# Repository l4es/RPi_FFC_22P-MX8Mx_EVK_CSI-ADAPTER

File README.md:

# RPi_FFC_22P-MX8Mx_EVK_CSI-ADAPTER

Adapter for Raspberry Pi compatible camera modules to iMX MiniSAS 36-pin camera interface, available in official NXP EVKs.

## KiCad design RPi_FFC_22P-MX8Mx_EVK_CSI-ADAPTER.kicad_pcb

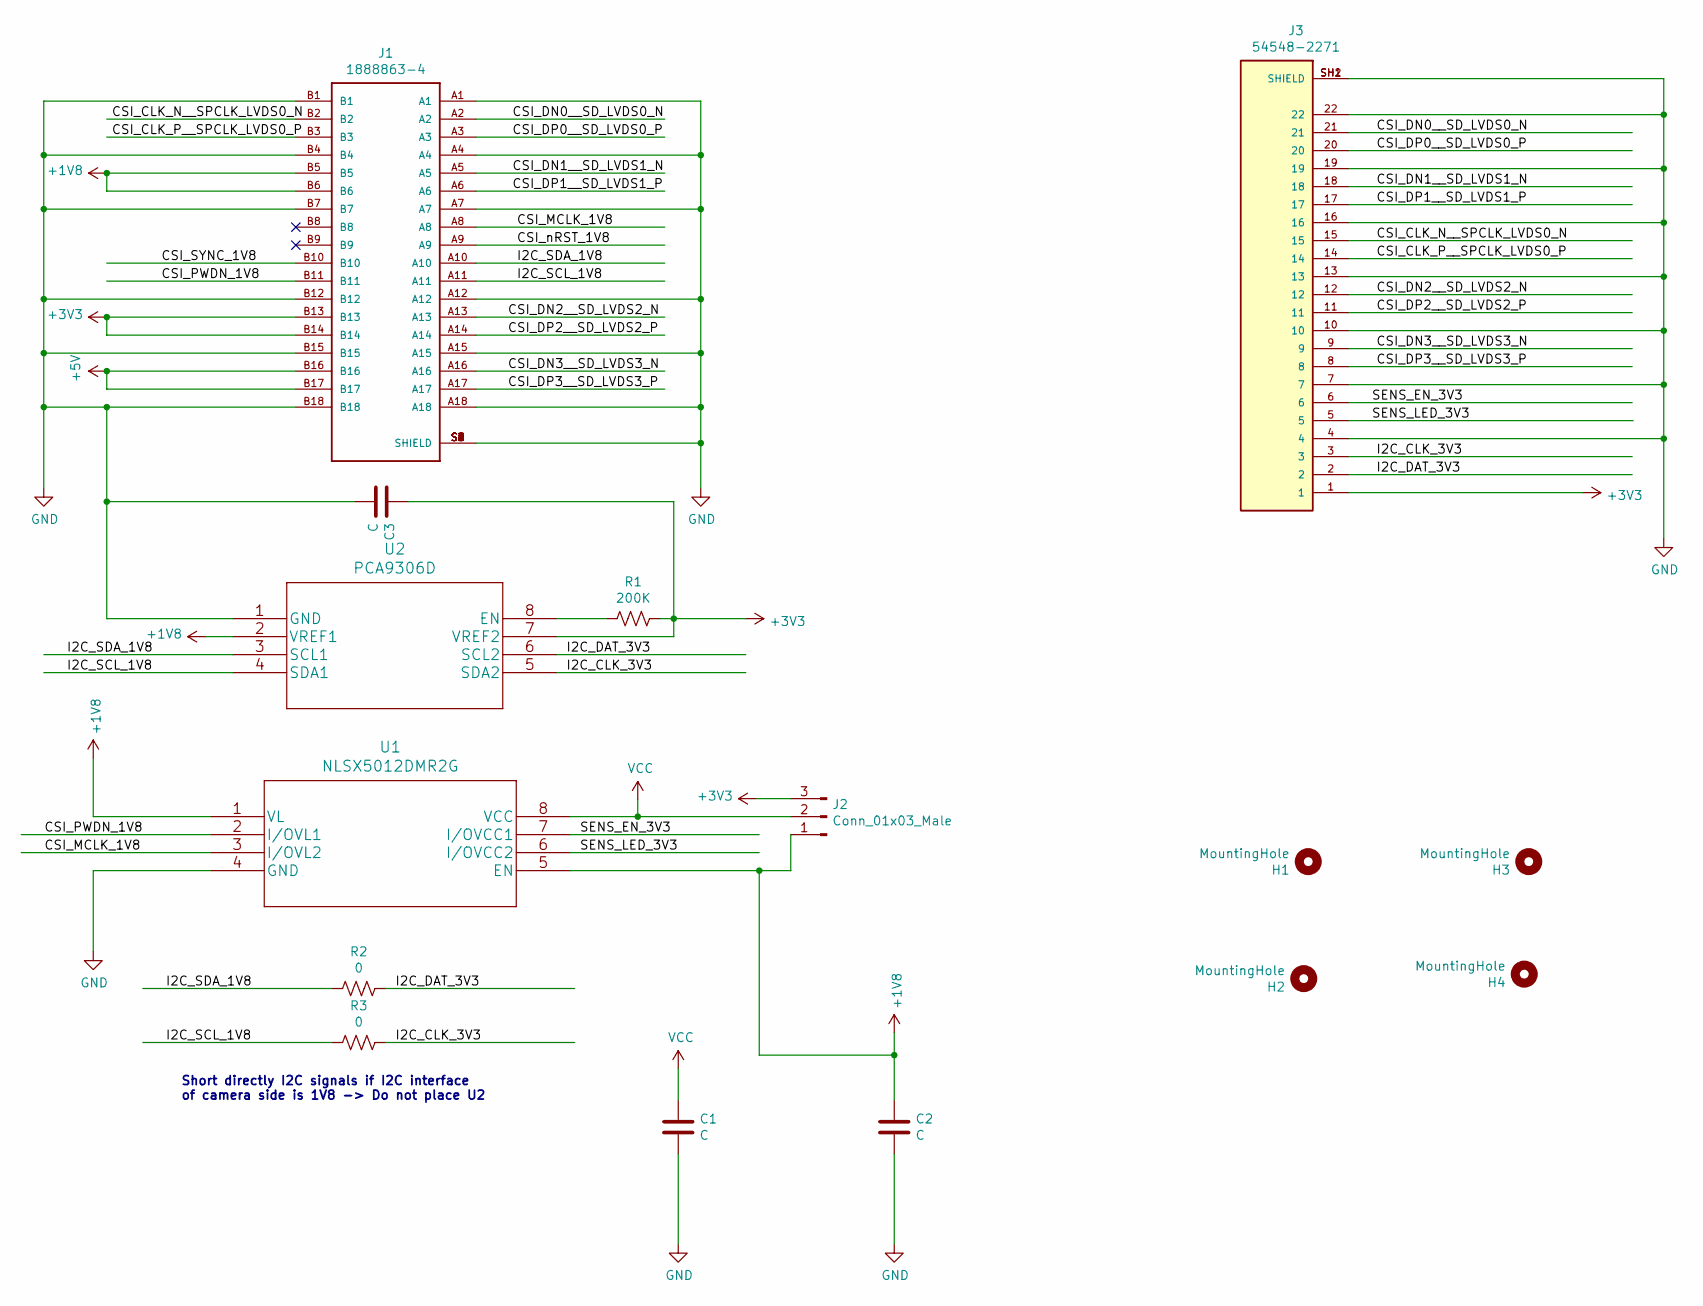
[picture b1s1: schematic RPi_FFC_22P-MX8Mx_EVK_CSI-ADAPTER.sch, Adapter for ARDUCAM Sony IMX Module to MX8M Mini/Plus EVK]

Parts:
C1, C2, C3: C; C_0603_1608Metric_Pad1.08x0.95mm_HandSolder
H1, H2, H3, H4: MountingHole; MountingHole_2.2mm_M2_Pad
J1: 1888863-4; TE_1888863-4
J2: Conn_01x03_Male; PinHeader_1x03_P2.54mm_Vertical
J3: 54548-2271; MOLEX_54548-2271; PARTREV N
R1: 200K; R_0805_2012Metric_Pad1.20x1.40mm_HandSolder
R2, R3: 0; R_0603_1608Metric_Pad0.98x0.95mm_HandSolder
U1: NLSX5012DMR2G
U2: PCA9306D

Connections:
+1V8: C2.1, J1.B5, J1.B6, J2.1, U1.1 (VL), U1.5 (EN), U2.2 (VREF1)
+3V3: C3.1, J1.B13, J1.B14, J2.3, J3.1, R1.1, U2.7 (VREF2)
+5V: J1.B16, J1.B17
/CSI_CLK_N__SPCLK_LVDS0_N: J1.B2, J3.15
/CSI_CLK_P__SPCLK_LVDS0_P: J1.B3, J3.14
/CSI_DN0__SD_LVDS0_N: J1.A2, J3.21
/CSI_DN1__SD_LVDS1_N: J1.A5, J3.18
/CSI_DN2__SD_LVDS2_N: J1.A13, J3.12
/CSI_DN3__SD_LVDS3_N: J1.A16, J3.9
/CSI_DP0__SD_LVDS0_P: J1.A3, J3.20
/CSI_DP1__SD_LVDS1_P: J1.A6, J3.17
/CSI_DP2__SD_LVDS2_P: J1.A14, J3.11
/CSI_DP3__SD_LVDS3_P: J1.A17, J3.8
/CSI_MCLK_1V8: J1.A8, U1.3 (I/OVL2)
/CSI_PWDN_1V8: J1.B11, U1.2 (I/OVL1)
/CSI_SYNC_1V8: J1.B10
/CSI_nRST_1V8: J1.A9
/I2C_CLK_3V3: J3.3, R3.1, U2.5 (SDA2)
/I2C_DAT_3V3: J3.2, R2.1, U2.6 (SCL2)
/I2C_SCL_1V8: J1.A11, R3.2, U2.4 (SDA1)
/I2C_SDA_1V8: J1.A10, R2.2, U2.3 (SCL1)
/SENS_EN_3V3: J3.6, U1.7 (I/OVCC1)
/SENS_LED_3V3: J3.5, U1.6 (I/OVCC2)
GND: C1.2, C2.2, C3.2, J1.A1, J1.A4, J1.A7, J1.A12, J1.A15, J1.A18, J1.B1, J1.B4, J1.B7, J1.B12, J1.B15, J1.B18, J1.S1 (SHIELD), J1.S2 (SHIELD), J1.S3 (SHIELD), J1.S4 (SHIELD), J1.S5 (SHIELD), J1.S6 (SHIELD), J1.S7 (SHIELD), J1.S8 (SHIELD), J3.4, J3.7, J3.10, J3.13, J3.16, J3.19, J3.22, J3.SH1 (SHIELD), J3.SH2 (SHIELD), U1.4 (GND), U2.1 (GND)
unnamed: R1.2, U2.8 (EN)
VCC: C1.1, J2.2, U1.8 (VCC)

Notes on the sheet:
Short directly I2C signals if I2C interface of camera side is 1V8 -> Do not place U2

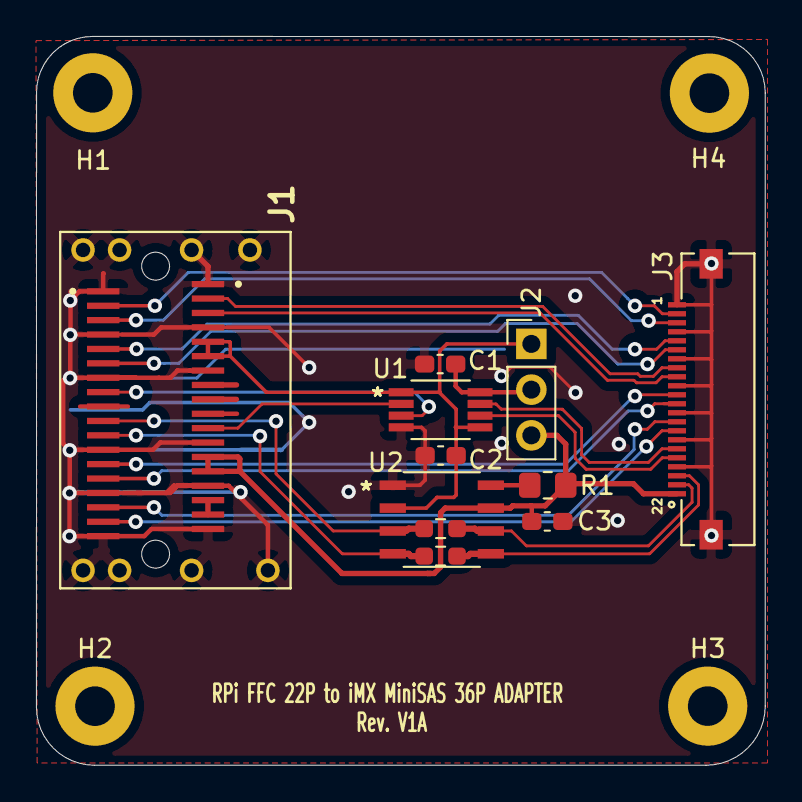
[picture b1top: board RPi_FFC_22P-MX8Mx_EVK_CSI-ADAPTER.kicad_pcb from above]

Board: 2 copper layers, 40.5 x 40.5 mm, 15 parts (0 on the bottom side), 24 nets.

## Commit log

2024-08-09 Add V1A revision
2024-08-09 Update documentation to show board's images

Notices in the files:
parts and their libraries:
Copyright 2021 Accelerated Designs. All rights reserved.
